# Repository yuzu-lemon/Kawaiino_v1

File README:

------------ Special Thanks ------------
ATmegaBOOT_168_atmega328_pro_8MHz.hex
  LGPL license
  https://github.com/arduino/ArduinoCore-avr
----------------------------------------

		  GNU LESSER GENERAL PUBLIC LICENSE
		       Version 2.1, February 1999

 Copyright (C) 1991, 1999 Free Software Foundation, Inc.
 51 Franklin Street, Fifth Floor, Boston, MA  02110-1301  USA
 Everyone is permitted to copy and distribute verbatim copies
 of this license document, but changing it is not allowed.

[This is the first released version of the Lesser GPL.  It also counts
 as the successor of the GNU Library Public License, version 2, hence
 the version number 2.1.]

			    Preamble

  The licenses for most software are designed to take away your
freedom to share and change it.  By contrast, the GNU General Public
Licenses are intended to guarantee your freedom to share and change
free software--to make sure the software is free for all its users.

  This license, the Lesser General Public License, applies to some
specially designated software packages--typically libraries--of the
Free Software Foundation and other authors who decide to use it.  You
can use it too, but we suggest you first think carefully about whether
this license or the ordinary General Public License is the better
strategy to use in any particular case, based on the explanations below.

  When we speak of free software, we are referring to freedom of use,
not price.  Our General Public Licenses are designed to make sure that
you have the freedom to distribute copies of free software (and charge
for this service if you wish); that you receive source code or can get
it if you want it; that you can change the software and use pieces of
it in new free programs; and that you are informed that you can do
these things.

  To protect your rights, we need to make restrictions that forbid
distributors to deny you these rights or to ask you to surrender these
rights.  These restrictions translate to certain responsibilities for
you if you distribute copies of the library or if you modify it.

  For example, if you distribute copies of the library, whether gratis
or for a fee, you must give the recipients all the rights that we gave
you.  You must make sure that they, too, receive or can get the source
code.  If you link other code with the library, you must provide
complete object files to the recipients, so that they can relink them
with the library after making changes to the library and recompiling
it.  And you must show them these terms so they know their rights.

  We protect your rights with a two-step method: (1) we copyright the
library, and (2) we offer you this license, which gives you legal
permission to copy, distribute and/or modify the library.

  To protect each distributor, we want to make it very clear that
there is no warranty for the free library.  Also, if the library is
modified by someone else and passed on, the recipients should know
that what they have is not the original version, so that the original
author's reputation will not be affected by problems that might be
introduced by others.

  Finally, software patents pose a constant threat to the existence of
any free program.  We wish to make sure that a company cannot
effectively restrict the users of a free program by obtaining a
restrictive license from a patent holder.  Therefore, we insist that
any patent license obtained for a version of the library must be
consistent with the full freedom of use specified in this license.

  Most GNU software, including some libraries, is covered by the
ordinary GNU General Public License.  This license, the GNU Lesser
General Public License, applies to certain designated libraries, and
is quite different from the ordinary General Public License.  We use
this license for certain libraries in order to permit linking those
libraries into non-free programs.

  When a program is linked with a library, whether statically or using
a shared library, the combination of the two is legally speaking a
combined work, a derivative of the original library.  The ordinary
General Public License therefore permits such linking only if the
entire combination fits its criteria of freedom.  The Lesser General
Public License permits more lax criteria for linking other code with
the library.

  We call this license the "Lesser" General Public License because it
does Less to protect the user's freedom than the ordinary General
Public License.  It also provides other free software developers Less
of an advantage over competing non-free programs.  These disadvantages
are the reason we use the ordinary General Public License for many
libraries.  However, the Lesser license provides advantages in certain
special circumstances.

  For example, on rare occasions, there may be a special need to
encourage the widest possible use of a certain library, so that it becomes
a de-facto standard.  To achieve this, non-free programs must be
allowed to use the library.  A more frequent case is that a free
library does the same job as widely used non-free libraries.  In this
case, there is little to gain by limiting the free library to free
software only, so we use the Lesser General Public License.

  In other cases, permission to use a particular library in non-free
programs enables a greater number of people to use a large body of
free software.  For example, permission to use the GNU C Library in
non-free programs enables many more people to use the whole GNU
operating system, as well as its variant, the GNU/Linux operating
system.

  Although the Lesser General Public License is Less protective of the
users' freedom, it does ensure that the user of a program that is
linked with the Library has the freedom and the wherewithal to run
that program using a modified version of the Library.

  The precise terms and conditions for copying, distribution and
modification follow.  Pay close attention to the difference between a
"work based on the library" and a "work that uses the library".  The
former contains code derived from the library, whereas the latter must
be combined with the library in order to run.

		  GNU LESSER GENERAL PUBLIC LICENSE
   TERMS AND CONDITIONS FOR COPYING, DISTRIBUTION AND MODIFICATION

  0. This License Agreement applies to any software library or other
program which contains a notice placed by the copyright holder or
other authorized party saying it may be distributed under the terms of
this Lesser General Public License (also called "this License").
Each licensee is addressed as "you".

  A "library" means a collection of software functions and/or data
prepared so as to be conveniently linked with application programs
(which use some of those functions and data) to form executables.

  The "Library", below, refers to any such software library or work
which has been distributed under these terms.  A "work based on the
Library" means either the Library or any derivative work under
copyright law: that is to say, a work containing the Library or a
portion of it, either verbatim or with modifications and/or translated
straightforwardly into another language.  (Hereinafter, translation is
included without limitation in the term "modification".)

  "Source code" for a work means the preferred form of the work for
making modifications to it.  For a library, complete source code means
all the source code for all modules it contains, plus any associated
interface definition files, plus the scripts used to control compilation
and installation of the library.

  Activities other than copying, distribution and modification are not
covered by this License; they are outside its scope.  The act of
running a program using the Library is not restricted, and output from
such a program is covered only if its contents constitute a work based
on the Library (independent of the use of the Library in a tool for
writing it).  Whether that is true depends on what the Library does
and what the program that uses the Library does.

  1. You may copy and distribute verbatim copies of the Library's
complete source code as you receive it, in any medium, provided that
you conspicuously and appropriately publish on each copy an
appropriate copyright notice and disclaimer of warranty; keep intact
all the notices that refer to this License and to the absence of any
warranty; and distribute a copy of this License along with the
Library.

  You may charge a fee for the physical act of transferring a copy,
and you may at your option offer warranty protection in exchange for a
fee.

  2. You may modify your copy or copies of the Library or any portion
of it, thus forming a work based on the Library, and copy and
distribute such modifications or work under the terms of Section 1
above, provided that you also meet all of these conditions:

    a) The modified work must itself be a software library.

    b) You must cause the files modified to carry prominent notices
    stating that you changed the files and the date of any change.

    c) You must cause the whole of the work to be licensed at no
    charge to all third parties under the terms of this License.

    d) If a facility in the modified Library refers to a function or a
    table of data to be supplied by an application program that uses
    the facility, other than as an argument passed when the facility
    is invoked, then you must make a good faith effort to ensure that,
    in the event an application does not supply such function or
    table, the facility still operates, and performs whatever part of
    its purpose remains meaningful.

    (For example, a function in a library to compute square roots has
    a purpose that is entirely well-defined independent of the
    application.  Therefore, Subsection 2d requires that any
    application-supplied function or table used by this function must
    be optional: if the application does not supply it, the square
    root function must still compute square roots.)

These requirements apply to the modified work as a whole.  If
identifiable sections of that work are not derived from the Library,
and can be reasonably considered independent and separate works in
themselves, then this License, and its terms, do not apply to those
sections when you distribute them as separate works.  But when you
distribute the same sections as part of a whole which is a work based
on the Library, the distribution of the whole must be on the terms of
this License, whose permissions for other licensees extend to the
entire whole, and thus to each and every part regardless of who wrote
it.

Thus, it is not the intent of this section to claim rights or contest
your rights to work written entirely by you; rather, the intent is to
exercise the right to control the distribution of derivative or
collective works based on the Library.

In addition, mere aggregation of another work not based on the Library
with the Library (or with a work based on the Library) on a volume of
a storage or distribution medium does not bring the other work under
the scope of this License.

  3. You may opt to apply the terms of the ordinary GNU General Public
License instead of this License to a given copy of the Library.  To do
this, you must alter all the notices that refer to this License, so
that they refer to the ordinary GNU General Public License, version 2,
instead of to this License.  (If a newer version than version 2 of the
ordinary GNU General Public License has appeared, then you can specify
that version instead if you wish.)  Do not make any other change in
these notices.

  Once this change is made in a given copy, it is irreversible for
that copy, so the ordinary GNU General Public License applies to all
subsequent copies and derivative works made from that copy.

  This option is useful when you wish to copy part of the code of
the Library into a program that is not a library.

  4. You may copy and distribute the Library (or a portion or
derivative of it, under Section 2) in object code or executable form
under the terms of Sections 1 and 2 above provided that you accompany
it with the complete corresponding machine-readable source code, which
must be distributed under the terms of Sections 1 and 2 above on a
medium customarily used for software interchange.

  If distribution of object code is made by offering access to copy
from a designated place, then offering equivalent access to copy the
source code from the same place satisfies the requirement to
distribute the source code, even though third parties are not
compelled to copy the source along with the object code.

  5. A program that contains no derivative of any portion of the
Library, but is designed to work with the Library by being compiled or
linked with it, is called a "work that uses the Library".  Such a
work, in isolation, is not a derivative work of the Library, and
therefore falls outside the scope of this License.

  However, linking a "work that uses the Library" with the Library
creates an executable that is a derivative of the Library (because it
contains portions of the Library), rather than a "work that uses the
library".  The executable is therefore covered by this License.
Section 6 states terms for distribution of such executables.

  When a "work that uses the Library" uses material from a header file
that is part of the Library, the object code for the work may be a
derivative work of the Library even though the source code is not.
Whether this is true is especially significant if the work can be
linked without the Library, or if the work is itself a library.  The
threshold for this to be true is not precisely defined by law.

  If such an object file uses only numerical parameters, data
structure layouts and accessors, and small macros and small inline
functions (ten lines or less in length), then the use of the object
file is unrestricted, regardless of whether it is legally a derivative
work.  (Executables containing this object code plus portions of the
Library will still fall under Section 6.)

  Otherwise, if the work is a derivative of the Library, you may
distribute the object code for the work under the terms of Section 6.
Any executables containing that work also fall under Section 6,
whether or not they are linked directly with the Library itself.

  6. As an exception to the Sections above, you may also combine or
link a "work that uses the Library" with the Library to produce a
work containing portions of the Library, and distribute that work
under terms of your choice, provided that the terms permit
modification of the work for the customer's own use and reverse
engineering for debugging such modifications.

  You must give prominent notice with each copy of the work that the
Library is used in it and that the Library and its use are covered by
this License.  You must supply a copy of this License.  If the work
during execution displays copyright notices, you must include the
copyright notice for the Library among them, as well as a reference
directing the user to the copy of this License.  Also, you must do one
of these things:

    a) Accompany the work with the complete corresponding
    machine-readable source code for the Library including whatever
    changes were used in the work (which must be distributed under
    Sections 1 and 2 above); and, if the work is an executable linked
    with the Library, with the complete machine-readable "work that
    uses the Library", as object code and/or source code, so that the
    user can modify the Library and then relink to produce a modified
    executable containing the modified Library.  (It is understood
    that the user who changes the contents of definitions files in the
    Library will not necessarily be able to recompile the application
    to use the modified definitions.)

    b) Use a suitable shared library mechanism for linking with the
    Library.  A suitable mechanism is one that (1) uses at run time a
    copy of the library already present on the user's computer system,
    rather than copying library functions into the executable, and (2)
    will operate properly with a modified version of the library, if
    the user installs one, as long as the modified version is
    interface-compatible with the version that the work was made with.

    c) Accompany the work with a written offer, valid for at
    least three years, to give the same user the materials
    specified in Subsection 6a, above, for a charge no more
    than the cost of performing this distribution.

    d) If distribution of the work is made by offering access to copy
    from a designated place, offer equivalent access to copy the above
    specified materials from the same place.

    e) Verify that the user has already received a copy of these
    materials or that you have already sent this user a copy.

  For an executable, the required form of the "work that uses the
Library" must include any data and utility programs needed for
reproducing the executable from it.  However, as a special exception,
the materials to be distributed need not include anything that is
normally distributed (in either source or binary form) with the major
components (compiler, kernel, and so on) of the operating system on
which the executable runs, unless that component itself accompanies
the executable.

  It may happen that this requirement contradicts the license
restrictions of other proprietary libraries that do not normally
accompany the operating system.  Such a contradiction means you cannot
use both them and the Library together in an executable that you
distribute.

  7. You may place library facilities that are a work based on the
Library side-by-side in a single library together with other library
facilities not covered by this License, and distribute such a combined
library, provided that the separate distribution of the work based on
the Library and of the other library facilities is otherwise
permitted, and provided that you do these two things:

    a) Accompany the combined library with a copy of the same work
    based on the Library, uncombined with any other library
    facilities.  This must be distributed under the terms of the
    Sections above.

    b) Give prominent notice with the combined library of the fact
    that part of it is a work based on the Library, and explaining
    where to find the accompanying uncombined form of the same work.

  8. You may not copy, modify, sublicense, link with, or distribute
the Library except as expressly provided under this License.  Any
attempt otherwise to copy, modify, sublicense, link with, or
distribute the Library is void, and will automatically terminate your
rights under this License.  However, parties who have received copies,
or rights, from you under this License will not have their licenses
terminated so long as such parties remain in full compliance.

  9. You are not required to accept this License, since you have not
signed it.  However, nothing else grants you permission to modify or
distribute the Library or its derivative works.  These actions are
prohibited by law if you do not accept this License.  Therefore, by
modifying or distributing the Library (or any work based on the
Library), you indicate your acceptance of this License to do so, and
all its terms and conditions for copying, distributing or modifying
the Library or works based on it.

  10. Each time you redistribute the Library (or any work based on the
Library), the recipient automatically receives a license from the
original licensor to copy, distribute, link with or modify the Library
subject to these terms and conditions.  You may not impose any further
restrictions on the recipients' exercise of the rights granted herein.
You are not responsible for enforcing compliance by third parties with
this License.

  11. If, as a consequence of a court judgment or allegation of patent
infringement or for any other reason (not limited to patent issues),
conditions are imposed on you (whether by court order, agreement or
otherwise) that contradict the conditions of this License, they do not
excuse you from the conditions of this License.  If you cannot
distribute so as to satisfy simultaneously your obligations under this
License and any other pertinent obligations, then as a consequence you
may not distribute the Library at all.  For example, if a patent
license would not permit royalty-free redistribution of the Library by
all those who receive copies directly or indirectly through you, then
the only way you could satisfy both it and this License would be to
refrain entirely from distribution of the Library.

If any portion of this section is held invalid or unenforceable under any
particular circumstance, the balance of the section is intended to apply,
and the section as a whole is intended to apply in other circumstances.

It is not the purpose of this section to induce you to infringe any
patents or other property right claims or to contest validity of any
such claims; this section has the sole purpose of protecting the
integrity of the free software distribution system which is
implemented by public license practices.  Many people have made
generous contributions to the wide range of software distributed
through that system in reliance on consistent application of that
system; it is up to the author/donor to decide if he or she is willing
to distribute software through any other system and a licensee cannot
impose that choice.

This section is intended to make thoroughly clear what is believed to
be a consequence of the rest of this License.

  12. If the distribution and/or use of the Library is restricted in
certain countries either by patents or by copyrighted interfaces, the
original copyright holder who places the Library under this License may add
an explicit geographical distribution limitation excluding those countries,
so that distribution is permitted only in or among countries not thus
excluded.  In such case, this License incorporates the limitation as if
written in the body of this License.

  13. The Free Software Foundation may publish revised and/or new
versions of the Lesser General Public License from time to time.
Such new versions will be similar in spirit to the present version,
but may differ in detail to address new problems or concerns.

Each version is given a distinguishing version number.  If the Library
specifies a version number of this License which applies to it and
"any later version", you have the option of following the terms and
conditions either of that version or of any later version published by
the Free Software Foundation.  If the Library does not specify a
license version number, you may choose any version ever published by
the Free Software Foundation.

  14. If you wish to incorporate parts of the Library into other free
programs whose distribution conditions are incompatible with these,
write to the author to ask for permission.  For software which is
copyrighted by the Free Software Foundation, write to the Free
Software Foundation; we sometimes make exceptions for this.  Our
decision will be guided by the two goals of preserving the free status
of all derivatives of our free software and of promoting the sharing
and reuse of software generally.

			    NO WARRANTY

  15. BECAUSE THE LIBRARY IS LICENSED FREE OF CHARGE, THERE IS NO
WARRANTY FOR THE LIBRARY, TO THE EXTENT PERMITTED BY APPLICABLE LAW.
EXCEPT WHEN OTHERWISE STATED IN WRITING THE COPYRIGHT HOLDERS AND/OR
OTHER PARTIES PROVIDE THE LIBRARY "AS IS" WITHOUT WARRANTY OF ANY
KIND, EITHER EXPRESSED OR IMPLIED, INCLUDING, BUT NOT LIMITED TO, THE
IMPLIED WARRANTIES OF MERCHANTABILITY AND FITNESS FOR A PARTICULAR
PURPOSE.  THE ENTIRE RISK AS TO THE QUALITY AND PERFORMANCE OF THE
LIBRARY IS WITH YOU.  SHOULD THE LIBRARY PROVE DEFECTIVE, YOU ASSUME
THE COST OF ALL NECESSARY SERVICING, REPAIR OR CORRECTION.

  16. IN NO EVENT UNLESS REQUIRED BY APPLICABLE LAW OR AGREED TO IN
WRITING WILL ANY COPYRIGHT HOLDER, OR ANY OTHER PARTY WHO MAY MODIFY
AND/OR REDISTRIBUTE THE LIBRARY AS PERMITTED ABOVE, BE LIABLE TO YOU
FOR DAMAGES, INCLUDING ANY GENERAL, SPECIAL, INCIDENTAL OR
CONSEQUENTIAL DAMAGES ARISING OUT OF THE USE OR INABILITY TO USE THE
LIBRARY (INCLUDING BUT NOT LIMITED TO LOSS OF DATA OR DATA BEING
RENDERED INACCURATE OR LOSSES SUSTAINED BY YOU OR THIRD PARTIES OR A
FAILURE OF THE LIBRARY TO OPERATE WITH ANY OTHER SOFTWARE), EVEN IF
SUCH HOLDER OR OTHER PARTY HAS BEEN ADVISED OF THE POSSIBILITY OF SUCH
DAMAGES.

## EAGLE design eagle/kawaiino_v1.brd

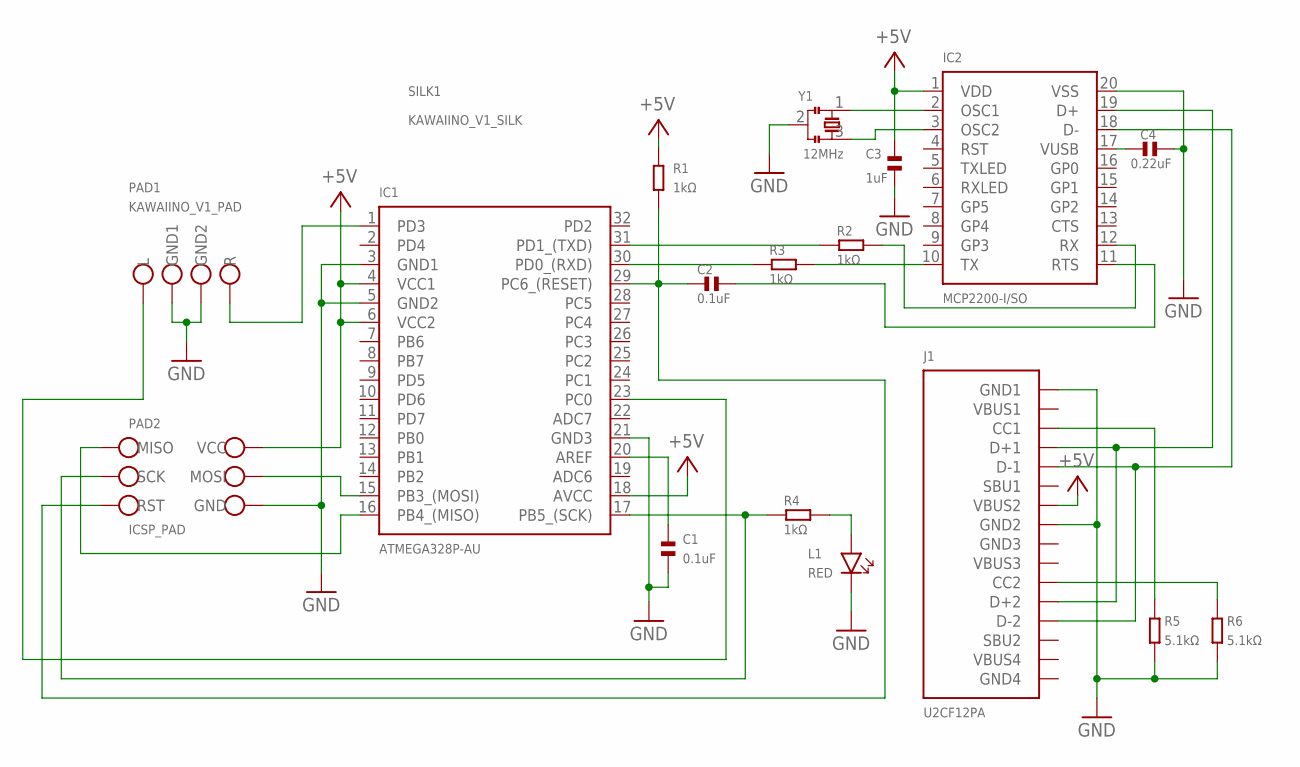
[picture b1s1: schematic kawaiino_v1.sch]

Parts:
C1, C2: 0.1uF; 1608_FOOTPRINT
C3: 1uF; 1608_FOOTPRINT
C4: 0.22uF; 1608_FOOTPRINT
IC1: ATMEGA328P-AU; TQFP-32
IC2: MCP2200-I/SO; SOIC20
J1: U2CF12PA; U2CF12PA_FOOTPRINT
L1: RED; 1608_FOOTPRINT
PAD1: KAWAIINO_V1_PAD
PAD2: ICSP_PAD
R1, R2, R3, R4: 1kΩ; 2012_FOOTPRINT
R5, R6: 5.1kΩ; 2012_FOOTPRINT
SILK1: KAWAIINO_V1_SILK
Y1: 12MHz; CSTNE_G_FOOTPRINT

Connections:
+5V: C3.1, IC1.4 (VCC1), IC1.6 (VCC2), IC1.18 (AVCC), IC2.1 (VDD), J1.7 (VBUS2), PAD2.2 (VCC), R1.1
GND: C1.2, C3.2, C4.2, IC1.3 (GND1), IC1.5 (GND2), IC1.21 (GND3), IC2.20 (VSS), J1.1 (GND1), J1.8 (GND2), L1.2 (-), PAD1.P$2 (GND1), PAD1.P$3 (GND2), PAD2.6 (GND), R5.2, R6.2, Y1.2
unnamed: IC1.30 (PD0_(RXD)), R3.1
unnamed: IC1.31 (PD1_(TXD)), R2.1
unnamed: IC2.10 (TX), R3.2
unnamed: IC2.12 (RX), R2.2
unnamed: C1.1, IC1.20 (AREF)
unnamed: C2.1, IC1.29 (PC6_(RESET)), PAD2.5 (RST), R1.2
unnamed: C4.1, IC2.17 (VUSB)
unnamed: IC2.2 (OSC1), Y1.1
unnamed: IC2.3 (OSC2), Y1.3
unnamed: IC1.1 (PD3), PAD1.P$4 (R)
unnamed: IC1.23 (PC0), PAD1.P$1 (L)
unnamed: IC1.15 (PB3_(MOSI)), PAD2.4 (MOSI)
unnamed: IC1.16 (PB4_(MISO)), PAD2.1 (MISO)
unnamed: IC1.17 (PB5_(SCK)), PAD2.3 (SCK), R4.1
unnamed: L1.1 (+), R4.2
unnamed: J1.11 (CC2), R6.1
unnamed: IC2.19 (D+), J1.4 (D+1), J1.12 (D+2)
unnamed: IC2.18 (D-), J1.5 (D-1), J1.13 (D-2)
unnamed: J1.3 (CC1), R5.1
unnamed: C2.2, IC2.11 (RTS)

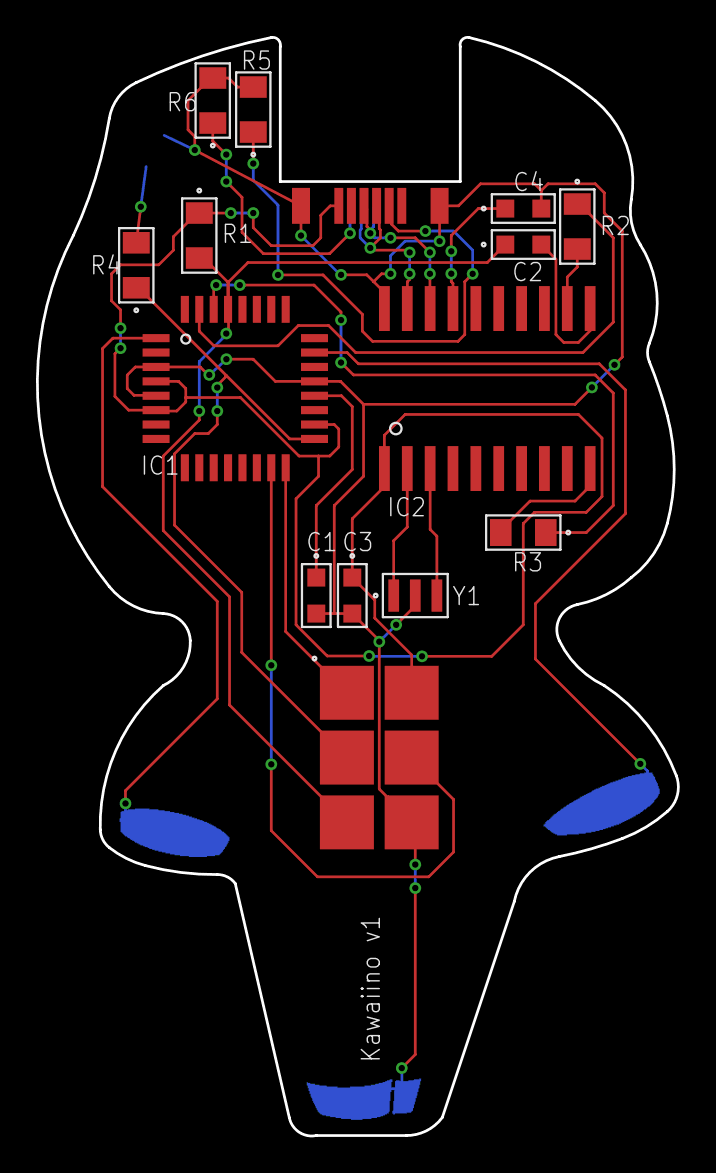
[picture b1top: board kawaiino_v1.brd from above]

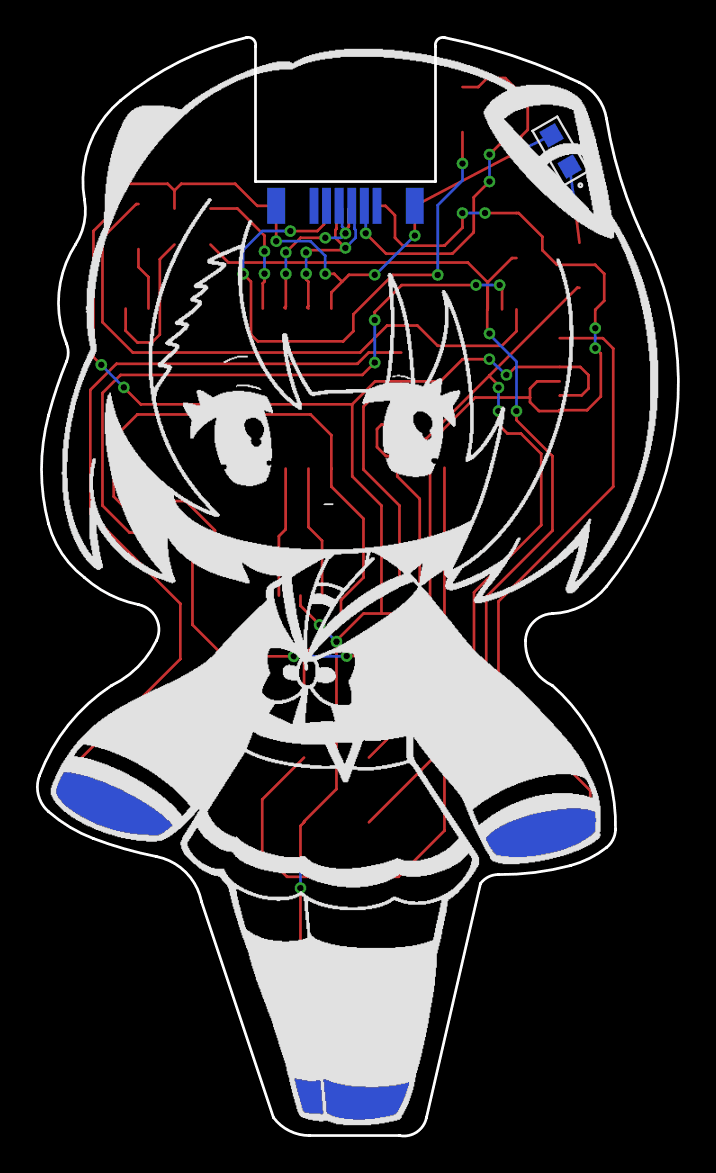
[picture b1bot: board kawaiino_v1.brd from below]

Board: 2 copper layers, 35.6 x 61.0 mm, 18 parts (3 on the bottom side), 22 nets.

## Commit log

2020-01-17 add board file
2020-01-28 add sketch files
2020-01-28 add LICENCE and README
2020-01-28 add eagle files
2020-01-28 add image
2020-01-28 add README.md
2020-01-29 add sketch files, remove sketch files
2020-02-09 fix licence
2020-02-10 change licence, fix copyright
2020-03-01 change licence

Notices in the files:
README:
the Library except as expressly provided under this License.  Any
rights under this License.  However, parties who have received copies,
or rights, from you under this License will not have their licenses
implemented by public license practices.  Many people have made
versions of the Lesser General Public License from time to time.
copyrighted by the Free Software Foundation, write to the Free
